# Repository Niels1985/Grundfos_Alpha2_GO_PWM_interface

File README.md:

# Grundfos_Alpha2_GO_PWM_interface
Arduino IDE sketch for ATtiny85 microcontroller. When pin 7 (PB2) is high a PWM from 11% tot 84% is on pin 6 (PB1). Pin 3 (PB4) is analog in for potentiometer to set the PWM from 11% to 84%. When digital in is off then 97% PWM is send. (97% = pump off)(11% to 84% = pump minimum rpm to pum maximum rpm).

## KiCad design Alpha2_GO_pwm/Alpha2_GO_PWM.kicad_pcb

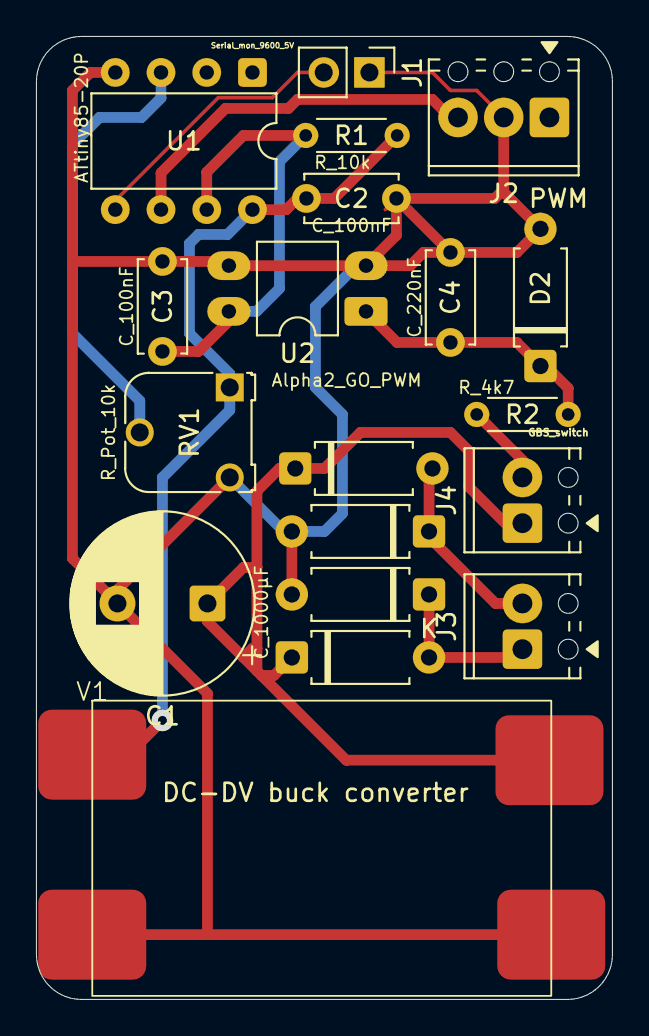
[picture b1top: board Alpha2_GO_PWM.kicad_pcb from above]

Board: 2 copper layers, 32.0 x 53.5 mm, 19 parts (0 on the bottom side), 11 nets.

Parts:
C1: C_1000µF; CP_Radial_D10.0mm_P5.00mm
C2, C3: C_100nF; C_Disc_D5.0mm_W2.5mm_P5.00mm
C4: C_220nF; C_Disc_D5.0mm_W2.5mm_P5.00mm
D2: D_1N4148; D_A-405_P7.62mm_Horizontal
D3, D4, D5, D6: D; D_A-405_P7.62mm_Horizontal
J1: Serial_mon_9600_5V; PinHeader_1x02_P2.54mm_Vertical
J2: PWM; TerminalBlock_Phoenix_MPT-0,5-3-2.54_1x03_P2.54mm_Horizontal
J3: Suply 24V~; TerminalBlock_Phoenix_MPT-0,5-2-2.54_1x02_P2.54mm_Horizontal
J4: GBS_switch; TerminalBlock_Phoenix_MPT-0,5-2-2.54_1x02_P2.54mm_Horizontal
R1: R_10k; R_Axial_DIN0204_L3.6mm_D1.6mm_P5.08mm_Horizontal
R2: R_4k7; R_Axial_DIN0204_L3.6mm_D1.6mm_P5.08mm_Horizontal
RV1: R_Pot_10k; Potentiometer_Runtron_RM-065_Vertical
U1: ATtiny85-20P; DIP-8_W7.62mm
U2: Optocoupler_DC_PhotoNPN_AKEC; DIP-4_W7.62mm_LongPads
V1: V100EY9

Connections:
+5V: C2.2, R1.1, RV1.1, U1.8 (VCC), V1.4 (Vout-)
+24V: C1.1, D3.1 (K), D4.1 (K), J4.1, V1.1 (Vin+)
GND: C1.2, C2.1, C3.1, C4.1, D2.2 (A), D5.2 (A), D6.2 (A), J1.1, J2.2, RV1.3, U1.4 (GND), U2.2, U2.3, V1.2 (Vin-), V1.3 (Vout+)
unnamed: C4.2, D2.1 (K), R2.2, U2.1
unnamed: D3.2 (A), D5.1 (K), J3.2
unnamed: D4.2 (A), D6.1 (K), J3.1
unnamed: J1.2, U1.5 (AREF/PB0)
unnamed: J2.3, U1.6 (PB1)
unnamed: J4.2, R2.1
unnamed: C3.2, R1.2, U1.7 (PB2), U2.4
unnamed: RV1.2, U1.3 (XTAL2/PB4)

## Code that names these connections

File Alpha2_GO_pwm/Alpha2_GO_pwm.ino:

// Niels Derksen 2026
// DEBUG info: PIN5 = (tegenover bolletje) Serieel TTL UART uit 9600 boud.
// Gebruik een TTL UART adapter op 5V voor uitlezing.
// Uit te lezen: Stand potmeter, PWM uitsturing, status digitaal in.


#include <Arduino.h>
#include <SoftwareSerial.h>

// ===== Pin mapping (ATtiny85 DIP-8) =====
// 1 = PB5/RESET  (niet gebruiken)
// 2 = PB3/ADC3   (vrij)
// 3 = PB4/ADC2   -> Potmeter wiper (ANALOG IN)
// 4 = GND
// 5 = PB0        -> Debug TX (SoftwareSerial TX-only)
// 6 = PB1/OC1A   -> PWM OUT naar pomp IN
// 7 = PB2        -> Digitale ingang (INPUT_PULLUP)
// 8 = VCC 5V

const uint8_t PIN_POT         = A2; // PB4, fysiek pin 3
const uint8_t PIN_PWM_OUT     = 1;  // PB1/OC1A, fysiek pin 6
const uint8_t PIN_DIGITAL_IN  = 2;  // PB2, fysiek pin 7
const uint8_t PIN_DBG_TX      = 0;  // PB0, fysiek pin 5

// Grundfos profiel A:
// 10..84% regelen, 95..100% standby/stop -> wij kiezen 98%
static const uint8_t DUTY_STANDBY = 98;
static const uint8_t DUTY_MIN     = 10;
static const uint8_t DUTY_MAX     = 84;

// 8 MHz -> 1 kHz: 8e6 / (64*(124+1)) = 1000 Hz
static const uint8_t TOP = 124;

// SoftwareSerial: RX pin is "dummy" (we gebruiken alleen TX)
SoftwareSerial dbg(255, PIN_DBG_TX); // RX=255 (niet gebruikt), TX=PB0

static inline uint8_t clamp_u8(int v, int lo, int hi) {
  if (v < lo) return (uint8_t)lo;
  if (v > hi) return (uint8_t)hi;
  return (uint8_t)v;
}

static void pwm_init_1kHz_OC1A() {
  pinMode(PIN_PWM_OUT, OUTPUT);

  TCCR1 = 0;
  GTCCR = 0;

  OCR1C = TOP;   // TOP bepaalt frequentie
  OCR1A = 0;     // duty

  // PWM op OC1A + prescaler /64
  TCCR1 = (1 << PWM1A) | (1 << COM1A1) | (1 << CS12) | (1 << CS11);
}

static void pwm_set_duty_percent(uint8_t dutyPercent) {
  dutyPercent = clamp_u8(dutyPercent, 0, 100);

  uint16_t ocr = (uint16_t)((uint32_t)dutyPercent * (uint32_t)(TOP + 1) + 50) / 100;
  if (ocr > TOP) ocr = TOP;
  OCR1A = (uint8_t)ocr;
}

static uint16_t read_pot_filtered() {
  uint32_t sum = 0;
  for (uint8_t i = 0; i < 8; i++) {
    sum += (uint16_t)analogRead(PIN_POT);
    delay(2);
  }
  return (uint16_t)(sum / 8);
}

void setup() {
  pinMode(PIN_DIGITAL_IN, INPUT_PULLUP); // los = HIGH, naar GND = LOW (actief)
  analogReference(DEFAULT);

  pwm_init_1kHz_OC1A();
  pwm_set_duty_percent(DUTY_STANDBY); // veilig starten: standby/stop

  dbg.begin(9600);
  dbg.println(F("ATtiny85 Alpha2GO PWM start"));
}

void loop() {
  // Inverted logic:
  // LOW (naar GND)  => regelmodus
  // HIGH (los)      => standby/stop
  const bool regelmodus = (digitalRead(PIN_DIGITAL_IN) == LOW);

  uint16_t adc = read_pot_filtered();           // 0..1023
  uint8_t potPercent = (uint8_t)((uint32_t)adc * 100UL / 1023UL);

  uint8_t dutyOut;

  if (!regelmodus) {
    dutyOut = DUTY_STANDBY;
  } else {
    int duty = DUTY_MIN + (int)((uint32_t)adc * (DUTY_MAX - DUTY_MIN) / 1023UL);
    dutyOut = clamp_u8(duty, DUTY_MIN, DUTY_MAX);
  }

  pwm_set_duty_percent(dutyOut);

  // Debug elke 3 seconden
  static uint32_t tLast = 0;
  uint32_t now = millis();
  if (now - tLast >= 3000UL) {
    tLast = now;

    dbg.print(F("IN="));
    dbg.print(regelmodus ? F("LOW(regel)") : F("HIGH(standby)"));

    dbg.print(F("  POT="));
    dbg.print(potPercent);
    dbg.print(F("%"));

    dbg.print(F("  PWM="));
    dbg.print(dutyOut);
    dbg.println(F("%"));
  }

  delay(20);
}

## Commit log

2026-02-11 V1.0
    Upload files
2026-02-13 V 10.1
    Details
2026-02-13 Added KiCad / Gerber
    Added KiCad / Gerber
